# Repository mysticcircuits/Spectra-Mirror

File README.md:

# Spectra-Mirror

The Spectra Mirror is an analog downsampler with a bunch of bells and whistles not found in other downsamplers.
The module is currently discontinued but is now available in an open hardware licence for those who still want
to build one.  Most of the well known DIY synth retailers as of now still have a few boards in stock, so if you
would like to build one without going through the process of getting the boards made yourself go ahead and
check them out, currently thonk, modular addict and synthcube all have them in stock.

The entire build is through hole with easy to find parts, there is one optional SMD matched transistor pair for 
those wanting superior tracking of the internal VCO.  I would say that this project is not for a complete beginner 
but would be quite easy for anyone with a fair amount of DIY experience.  The calibration procedure requires at 
least a multimeter and benefits from the use of an oscilloscope, although again this is not crucial.  Please read 
the build documentation if you want a better idea of the level of difficulty for the build.

For any questions or comments please visit the MW thread here 
https://www.muffwiggler.com/forum/viewtopic.php?p=2418444#2418444

========= FOR THOSE ATTEMPTING THE MATCHED TRANSISTOR PAIR =========

The following parts will be needed.  I am specifically making you source them as a "barrier for entry" as doing 
this matched transistor pair is not for DIY beginners.  SMD soldering aptitude is required.

Transistor pair is by diodes incorporated part # ZXTC2045E6TA

You will also need a 22k resistor and a 22nF capacitor.

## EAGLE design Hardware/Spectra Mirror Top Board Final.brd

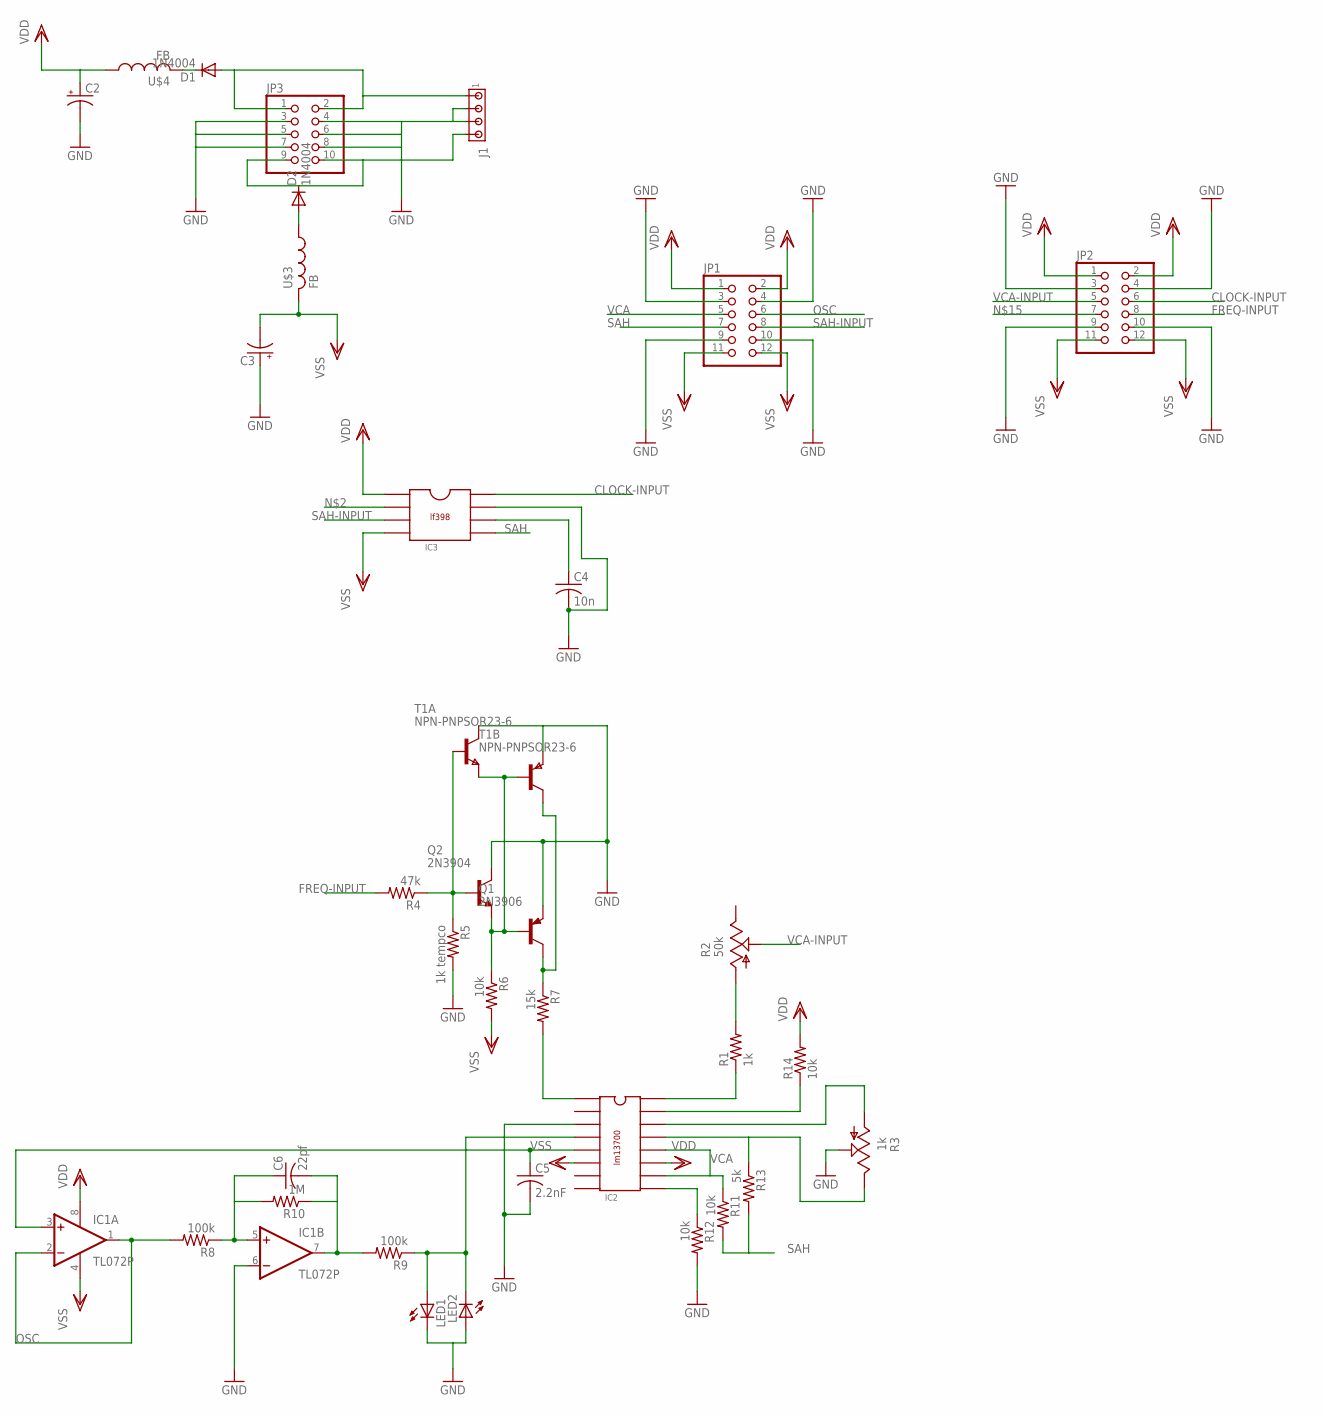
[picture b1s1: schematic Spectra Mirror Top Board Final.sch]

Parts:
C2, C3: CPOL-USE2.5-5; E2,5-5
C4: 10n; C050-024X044
C5: 2.2nF; C050-024X044
C6: 22pf; C050-024X044
D1, D2: 1N4004; DO41-10
IC1: TL072P; DIL08
IC2: LM13700; DIL16
IC3: LF398; DIL08
J1: MTA04-156; 1X4MTA
JP1, JP2: PINHD-2X6; 2X06
JP3: PINHD-2X5; 2X05
LED1, LED2: LED3MM
Q1: 2N3906; TO92
Q2: 2N3904; TO92
R1: 1k; 0204/7
R2: 50k; B64Y
R3: 1k; B64Y
R4: 47k; 0204/7
R5: 1k tempco; 0204/7
R6, R11, R12, R14: 10k; 0204/7
R7: 15k; 0204/7
R8, R9: 100k; 0204/7
R10: 1M; 0204/7
R13: 5k; 0204/7
T1: NPN-PNPSOR23-6; SOT23-6
U$3, U$4: FB

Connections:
CLOCK-INPUT: IC3.8, JP2.6
FREQ-INPUT: JP2.8, R4.2
GND: C2.-, C3.+, C4.2, C5.2, IC1.6 (-IN), IC2.3, IC3.7, J1.2, J1.3, JP1.3, JP1.4, JP1.9, JP1.10, JP2.3, JP2.4, JP2.9, JP2.10, JP3.3, JP3.4, JP3.5, JP3.6, JP3.7, JP3.8, LED1.K (C), LED2.A, Q1.3 (E), Q2.1 (C), R3.S, R5.2, R12.2, T1.1 (C), T1.4 (E)
unnamed: D1.A, J1.1, JP3.1, JP3.2
unnamed: Q1.2 (B), Q2.3 (E), R6.1, T1.5 (B), T1.6 (E)
unnamed: Q2.2 (B), R4.1, R5.1, T1.2 (B)
unnamed: C4.1, IC3.6
unnamed: C6.1, IC1.5 (+IN), R8.1, R10.2
unnamed: Q1.1 (C), R7.1, T1.3 (C)
unnamed: IC2.1, R7.2
unnamed: IC2.4, LED1.A, LED2.K (C), R9.1
unnamed: C6.2, IC1.7 (OUT), R9.2, R10.1
unnamed: D2.C, J1.4, JP3.9, JP3.10
unnamed: C5.1, IC1.3 (+IN), IC2.5
unnamed: IC2.9, R12.1
unnamed: IC2.13, R3.E, R13.1
unnamed: IC2.14, R3.A
unnamed: IC2.15, R14.1
unnamed: IC2.16, R1.1
unnamed: R1.2, R2.A
unnamed: D1.C, U$4.P$2 (2)
unnamed: D2.A, U$3.P$1 (1)
OSC: IC1.1 (OUT), IC1.2 (-IN), JP1.6, R8.2
SAH: IC3.5, JP1.7, R11.2, R13.2
SAH-INPUT: IC3.3, JP1.8
VCA: IC2.10, IC2.12, JP1.5, R11.1
VCA-INPUT: JP2.5, R2.S
VDD: C2.+, IC1.8 (V+), IC2.11, IC3.1, JP1.1, JP1.2, JP2.1, JP2.2, R14.2, U$4.P$1 (1)
VSS: C3.-, IC1.4 (V-), IC2.6, IC3.4, JP1.11, JP1.12, JP2.11, JP2.12, R6.2, U$3.P$2 (2)

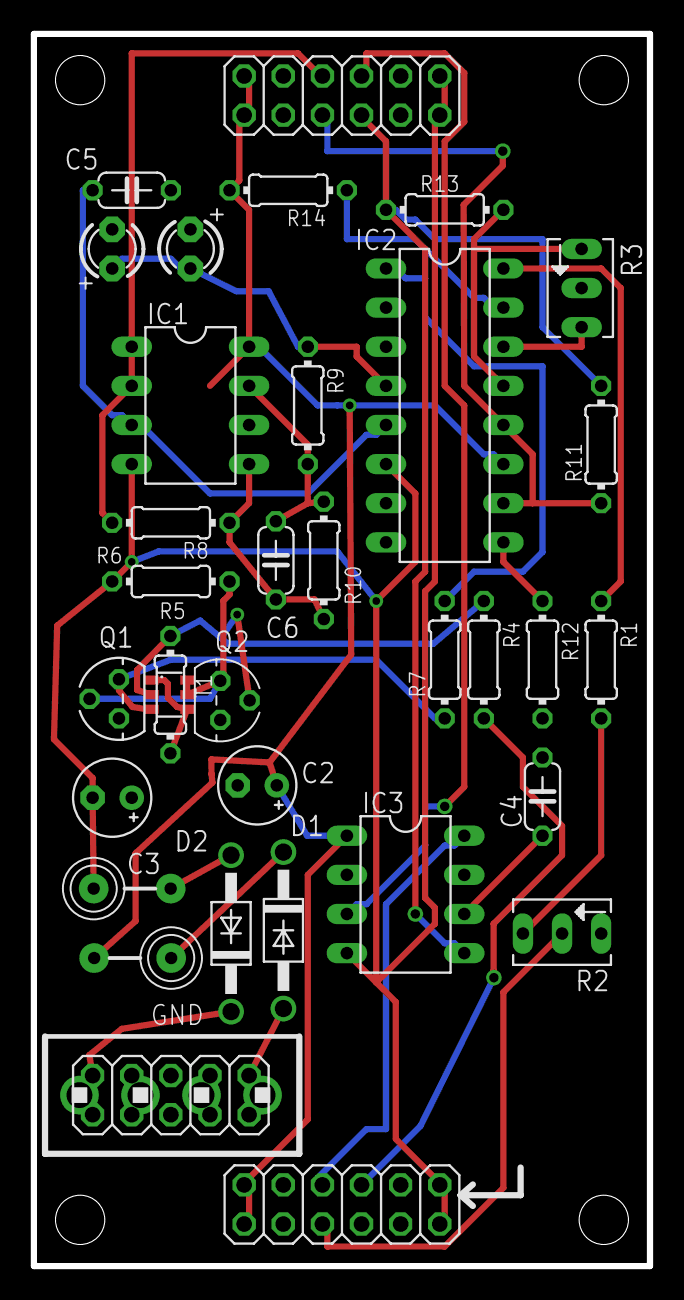
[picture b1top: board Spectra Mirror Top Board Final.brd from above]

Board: 2 copper layers, 40.0 x 80.0 mm, 35 parts (0 on the bottom side), 29 nets.

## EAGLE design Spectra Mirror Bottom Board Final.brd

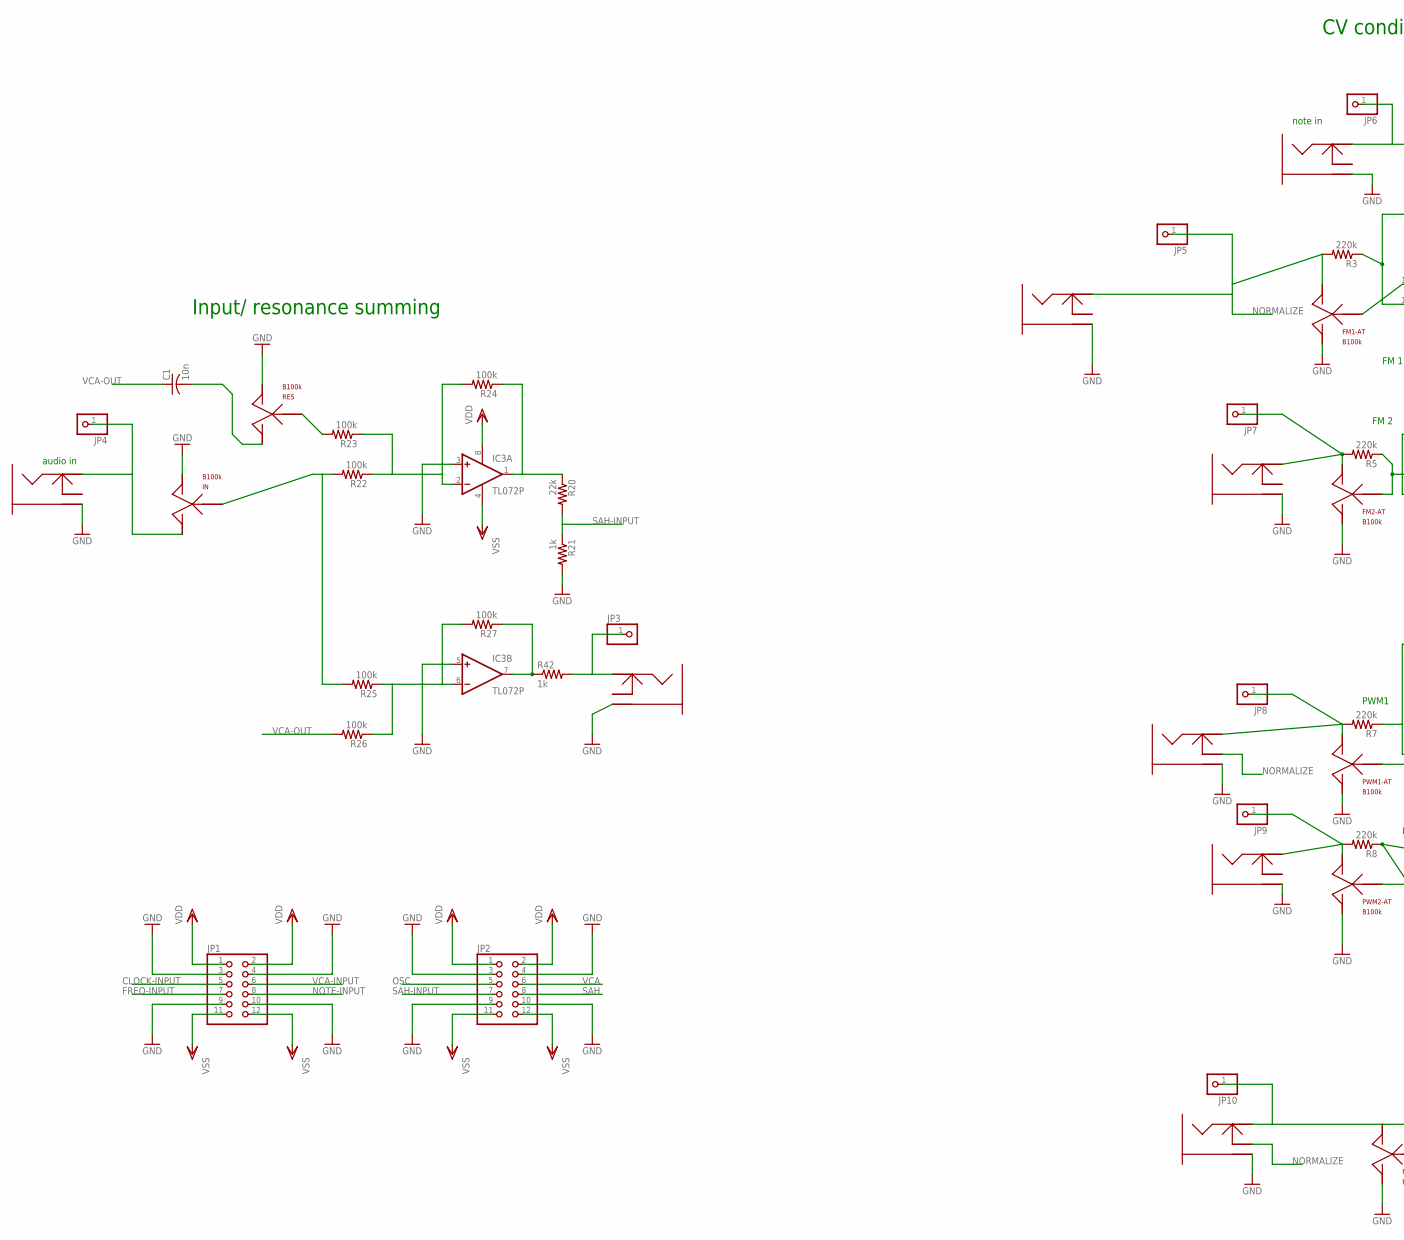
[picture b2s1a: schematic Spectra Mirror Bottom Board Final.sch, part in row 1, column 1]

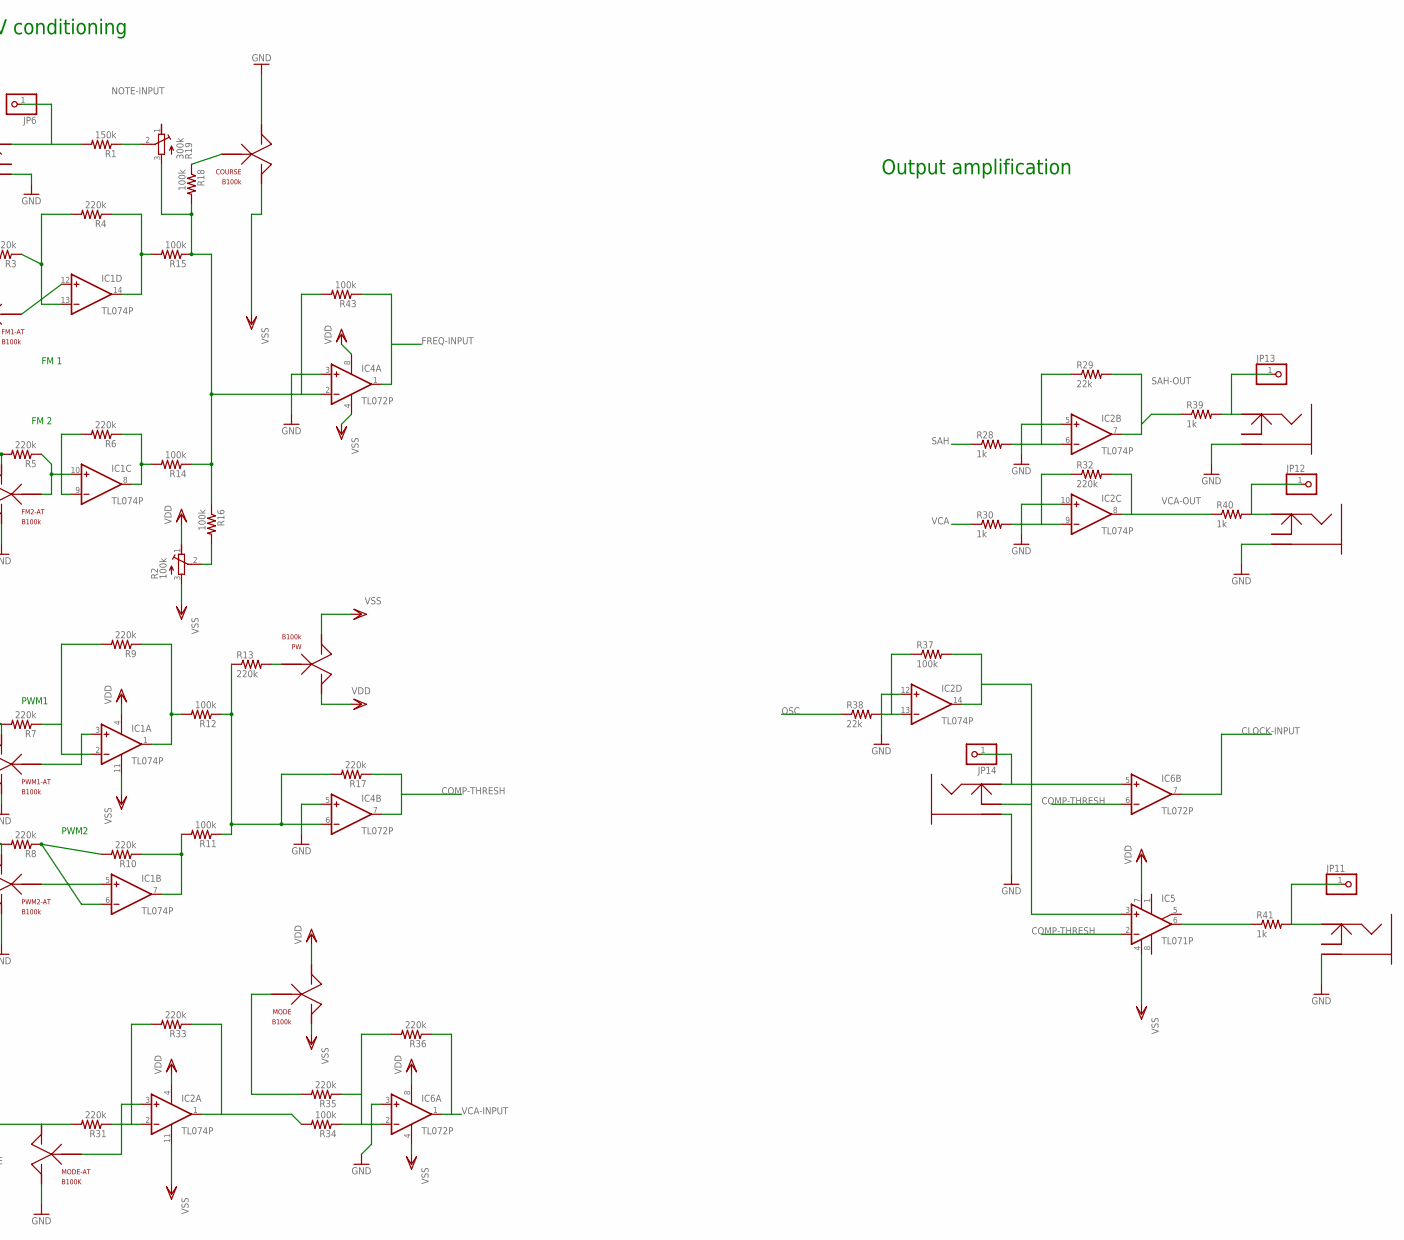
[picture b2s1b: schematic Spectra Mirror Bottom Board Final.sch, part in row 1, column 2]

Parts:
C1: 10n; C050-025X075
COURSE: B100k; ALPHAPOT_BOARDMOUNT
FM1-AT, FM2-AT: B100k; ALPHAPOT_BOARDMOUNT
IC1, IC2: TL074P; DIL14
IC3, IC4, IC6: TL072P; DIL08
IC5: TL071P; DIL08
IN: B100k; ALPHAPOT_BOARDMOUNT
JP1, JP2: PINHD-2X6; 2X06
JP3, JP4, JP5, JP6, JP7, JP8, JP9, JP10, JP11, JP12, JP13, JP14: PINHD-1X1; 1X01
MODE: B100k; ALPHAPOT_BOARDMOUNT
MODE-AT: B100K; ALPHAPOT_BOARDMOUNT
PW: B100k; ALPHAPOT_BOARDMOUNT
PWM1-AT, PWM2-AT: B100k; ALPHAPOT_BOARDMOUNT
R1: 150k; 0204/7
R2: 100k; RTRIMT93YA
R3, R5, R7, R8, R10, R13, R17, R31, R32, R35, R36: 220k; 0204/7
R4, R6, R9, R33: 220k; 0204V
R11, R12, R14, R15, R16, R18, R22, R23, R24, R25, R26, R27, R34, R43: 100k; 0204/7
R19: 300k; RTRIMT93YA
R20, R38: 22k; 0204/7
R21, R28, R30, R39, R40, R41, R42: 1k; 0204/7
R29: 22k; 0204V
R37: 100k; 0204V
RES: B100k; ALPHAPOT_BOARDMOUNT
U$1, U$2, U$3, U$4, U$5, U$6, U$7, U$8, U$9, U$10, U$11, U$12: KOBICONPJ-301

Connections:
CLOCK-INPUT: IC6.7 (OUT), JP1.5
COMP-THRESH: IC4.7 (OUT), IC5.2 (-IN), IC6.6 (-IN), R17.1
FREQ-INPUT: IC4.1 (OUT), JP1.7, R43.1
GND: COURSE.LEFT, FM1-AT.RIGHT, FM2-AT.RIGHT, IC2.5 (+IN), IC2.10 (+IN), IC2.12 (+IN), IC3.3 (+IN), IC3.5 (+IN), IC4.3 (+IN), IC4.5 (+IN), IC6.3 (+IN), IN.RIGHT, JP1.3, JP1.4, JP1.9, JP1.10, JP2.3, JP2.4, JP2.9, JP2.10, MODE-AT.RIGHT, PWM1-AT.RIGHT, PWM2-AT.RIGHT, R21.2, RES.RIGHT, U$1.GND (GROUND), U$1.GND2 (GROUND), U$2.GND (GROUND), U$2.GND2 (GROUND), U$3.GND (GROUND), U$3.GND2 (GROUND), U$4.GND (GROUND), U$4.GND2 (GROUND), U$5.GND (GROUND), U$5.GND2 (GROUND), U$6.GND (GROUND), U$6.GND2 (GROUND), U$7.GND (GROUND), U$7.GND2 (GROUND), U$8.GND (GROUND), U$8.GND2 (GROUND), U$9.GND (GROUND), U$9.GND2 (GROUND), U$10.GND (GROUND), U$10.GND2 (GROUND), U$11.GND (GROUND), U$11.GND2 (GROUND), U$12.GND (GROUND), U$12.GND2 (GROUND)
KJDNFKDNF: IC1.13 (-IN), R3.1, R4.2
unnamed: R1.1, R19.2 (S)
unnamed: R2.2 (S), R16.2
unnamed: IC5.6 (OUT), R41.1
unnamed: IC1.14 (OUT), R4.1, R15.2
unnamed: FM1-AT.MID, IC1.12 (+IN)
unnamed: FM2-AT.MID, IC1.10 (+IN), R5.1
unnamed: IC1.9 (-IN), R6.2
unnamed: FM2-AT.LEFT, JP7.1, R5.2, U$4.IN (INPUT)
unnamed: IC1.8 (OUT), R6.1, R14.2
unnamed: JP9.1, PWM2-AT.LEFT, R8.2, U$11.IN (INPUT)
unnamed: IC1.6 (-IN), R8.1, R10.2
unnamed: JP8.1, PWM1-AT.LEFT, R7.2, U$12.IN (INPUT)
unnamed: IC1.2 (-IN), R7.1, R9.2
unnamed: IC1.1 (OUT), R9.1, R12.2
unnamed: IC1.3 (+IN), PWM1-AT.MID
unnamed: IC1.5 (+IN), PWM2-AT.MID
unnamed: IC1.7 (OUT), R10.1, R11.2
unnamed: IC4.6 (-IN), R11.1, R12.1, R13.1, R17.2
unnamed: PW.MID, R13.2
unnamed: IC4.2 (-IN), R14.1, R15.1, R16.1, R18.2, R19.3 (A), R43.2
unnamed: COURSE.MID, R18.1
unnamed: JP10.1, MODE-AT.LEFT, R31.2, U$10.IN (INPUT)
unnamed: IN.LEFT, JP4.1, U$1.IN (INPUT)
unnamed: IN.MID, R22.2, R25.2
unnamed: IC3.6 (-IN), R25.1, R26.1, R27.2
unnamed: IC3.1 (OUT), R20.1, R24.1
unnamed: IC2.2 (-IN), R31.1, R33.2
unnamed: IC3.2 (-IN), R22.1, R23.1, R24.2
unnamed: IC3.7 (OUT), R27.1, R42.1
unnamed: R23.2, RES.MID
unnamed: IC2.1 (OUT), R33.1, R34.2
unnamed: IC2.9 (-IN), R30.2, R32.1
unnamed: IC2.3 (+IN), MODE-AT.MID
unnamed: IC2.6 (-IN), R28.2, R29.1
unnamed: C1.2, RES.LEFT
unnamed: IC6.2 (-IN), R34.1, R35.1, R36.2
unnamed: IC2.13 (-IN), R37.1, R38.2
unnamed: IC2.14 (OUT), IC5.3 (+IN), R37.2, U$9.SWITCH
unnamed: MODE.MID, R35.2
unnamed: IC6.5 (+IN), JP14.1, U$9.IN (INPUT)
unnamed: JP11.1, R41.2, U$5.IN (INPUT)
unnamed: JP12.1, R40.2, U$7.IN (INPUT)
unnamed: JP13.1, R39.2, U$6.IN (INPUT)
unnamed: JP3.1, R42.2, U$8.IN (INPUT)
NORMALIZE: FM1-AT.LEFT, JP5.1, R3.2, U$3.IN (INPUT), U$10.SWITCH, U$12.SWITCH
NOTE-INPUT: JP1.8, JP6.1, R1.2, U$2.IN (INPUT)
OSC: JP2.5, R38.1
SAH: JP2.8, R28.1
SAH-INPUT: JP2.7, R20.2, R21.1
SAH-OUT: IC2.7 (OUT), R29.2, R39.1
VCA: JP2.6, R30.1
VCA-INPUT: IC6.1 (OUT), JP1.6, R36.1
VCA-OUT: C1.1, IC2.8 (OUT), R26.2, R32.2, R40.1
VDD: IC1.4 (V+), IC2.4 (V+), IC3.8 (V+), IC4.8 (V+), IC5.7 (V+), IC6.8 (V+), JP1.1, JP1.2, JP2.1, JP2.2, MODE.LEFT, PW.LEFT, R2.1 (E)
VSS: COURSE.RIGHT, IC1.11 (V-), IC2.11 (V-), IC3.4 (V-), IC4.4 (V-), IC5.4 (V-), IC6.4 (V-), JP1.11, JP1.12, JP2.11, JP2.12, MODE.RIGHT, PW.RIGHT, R2.3 (A)

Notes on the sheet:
note in
FM 1
FM 2
audio in
PWM1
PWM2
Input/ resonance summing
CV conditioning
Output amplification

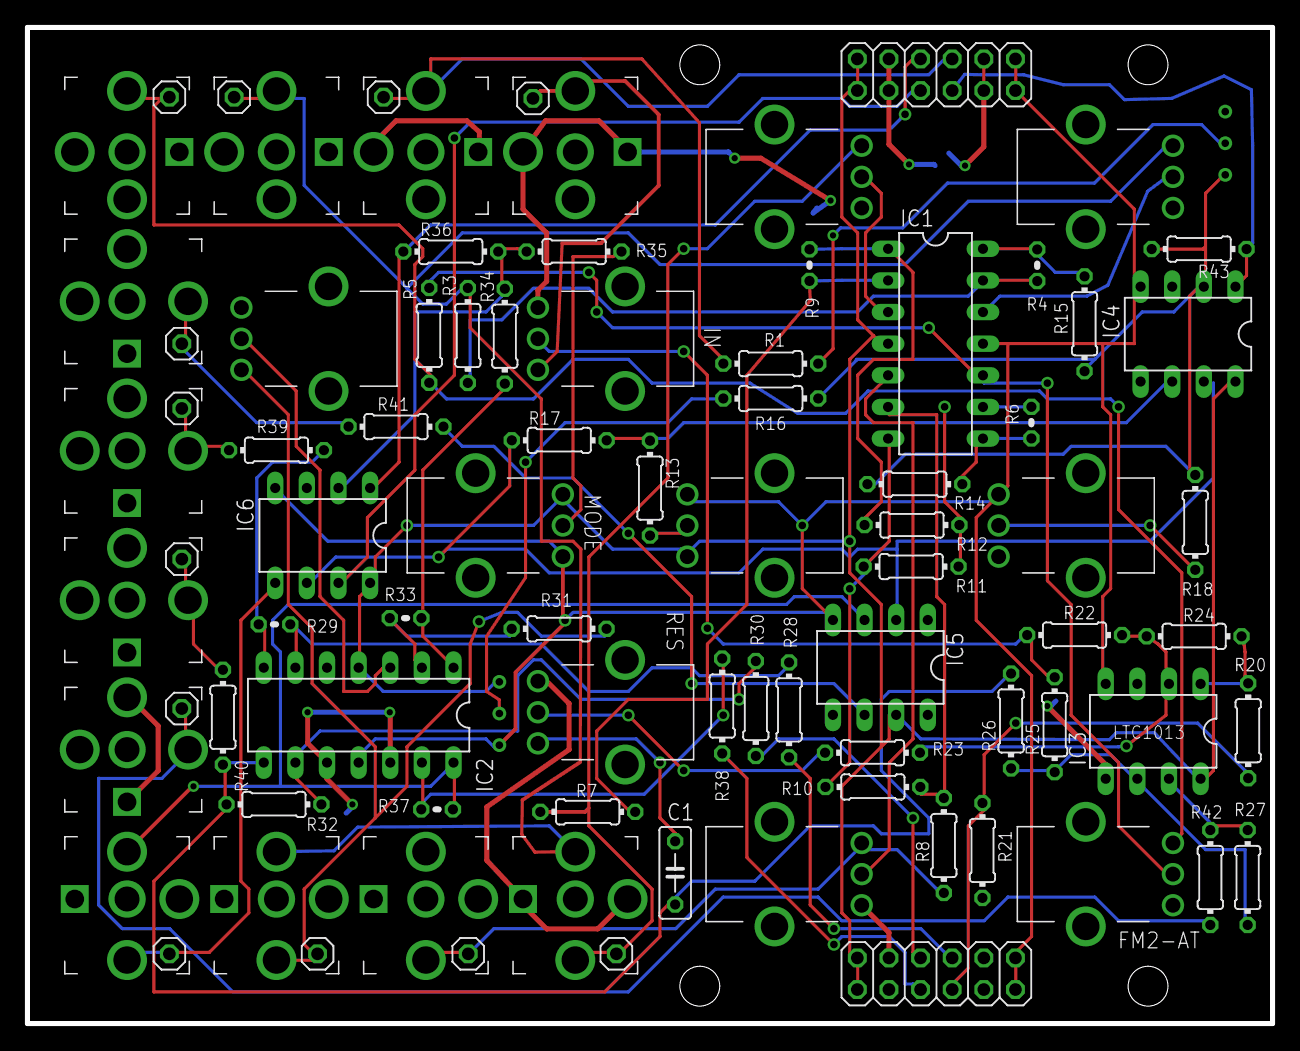
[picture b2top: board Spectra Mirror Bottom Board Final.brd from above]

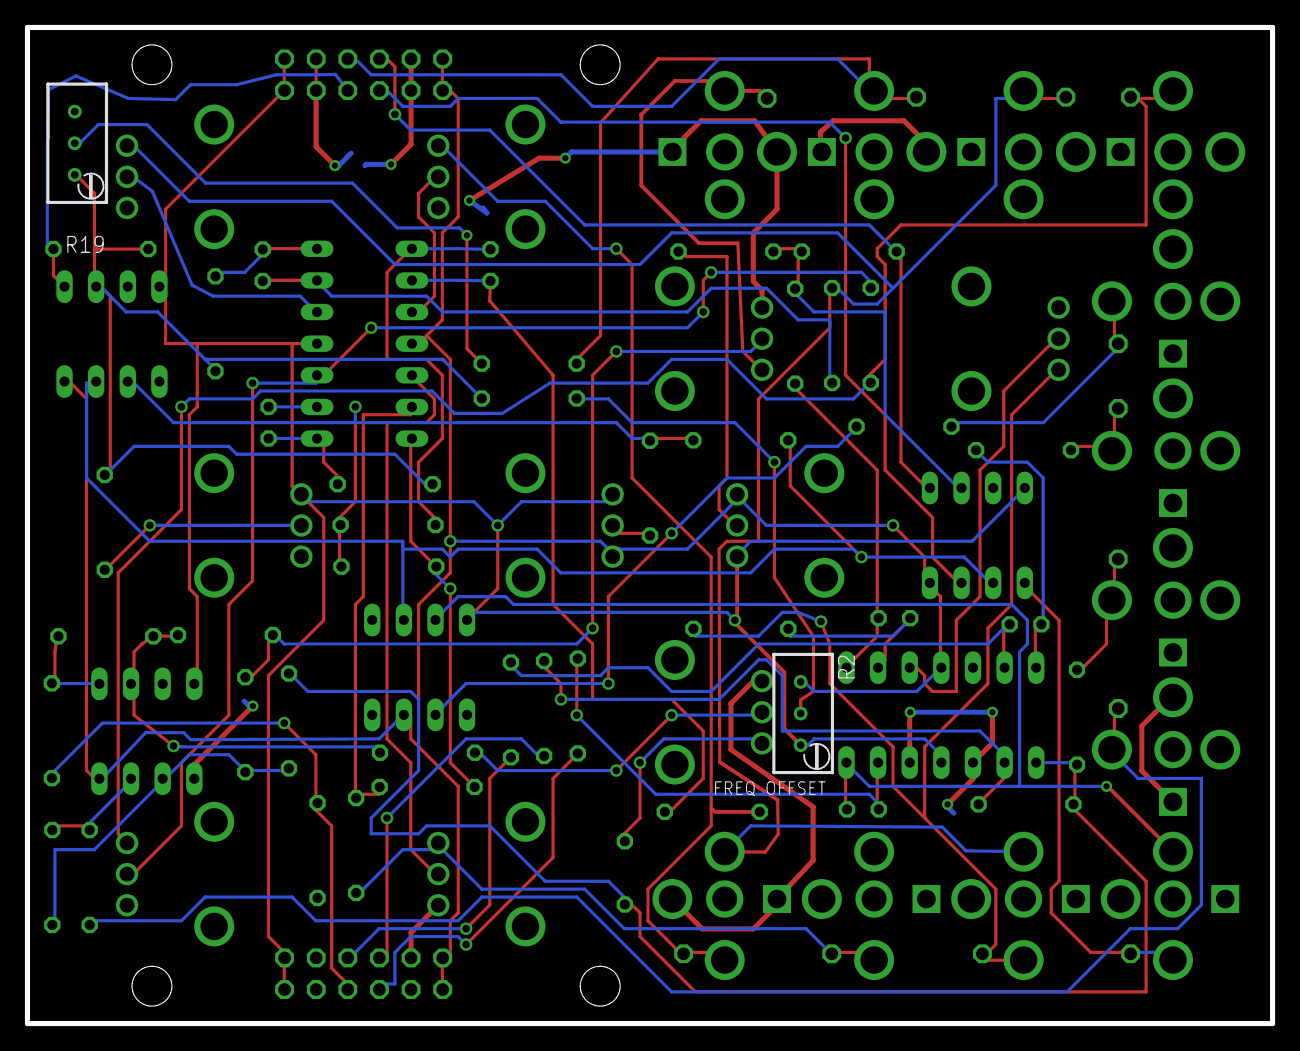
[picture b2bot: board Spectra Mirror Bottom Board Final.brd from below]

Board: 2 copper layers, 100.0 x 80.0 mm, 86 parts (2 on the bottom side), 60 nets.

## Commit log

2019-05-06 Create dfdfdf
2019-05-06 Create llklk
2019-05-06 Create licence

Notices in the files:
Hardware/Spectra Mirror Top Board Final.brd:
All Rights Reserved
